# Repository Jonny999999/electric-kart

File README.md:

Firmware for Atmega-8 Microcontroller and kicad PCB-Files for a custom built electric kart.  
**Note:** The firmware and PCB files Version V1 were originally created in 2015, those have been added to this repository for archival purposes.

<br>

# Hardware Overview (vehicle)
- 2.9 kW Series wound motor (forklift)
- Custom pcb with Atmega-8 creating 124 Hz PWM
- Custom pcb with mosfet driver
- Custom pcb with relay on IGBT for emergency stop
- Audi gas pedal used as voltage divider 
- 600A IGBT (FUJI 1MBI600PX-140-01)
- Schottky diode

## Wiring plan
[doc/wiring-plan.drawio.pdf](doc/wiring-plan.drawio.pdf)
  
## Photos

<br>

# Firmware
## Requirements
- avr-gcc
- avrdude
- make

## Compile
```bash
cd firmware/V1_fw-control-board
make
```

## Flash
Connect laptop to the board using an USB ISB-Programmer and run the commands:
```bash
make &&
sudo make upload
```
Note: `make upload` flashes the last compiled .elf file only  
-> also run `make` first for compiling and flashing the latest version.

## Current version
The current actually used project is located in [firmware/V2.1/](firmware/V2.1/).  
All other folders in [firmware/](firmware/) are for old board versions thus no longer used and archive only.

<br>

# Hardware (PCB Versions)
## V2.1
Rework of version V2.0 with more effort put into EMC to fix controller resets:
- 2 layer board
- 5V/GND for controller completely isolated from main batteries
  - isolated 5V DC-DC converter IC
  - more optocouplers: for driver, mosfet, relay and batt-voltage-threshold
- Strictly separate 5V and 24V components (separate GND planes, isolation gap)
- Front side is GND layer, Back side also has GND zones

Date: 2024.08.20  
Folder: [hardware/V2.1_board-ecar_isolated](hardware/V2.1_board-ecar_isolated/)  
Schematic: [hardware/V2.1_board-ecar_isolated/export/schematic.pdf](hardware/V2.1_board-ecar_isolated/export/schematic.pdf)
<br>
<br>

## V2.0
V1.1 worked well for almost 9 years, the idea was to replace the corroded pcb and get rid of the separate supply batteries for the control board.  
Single board with controller, driver and newly added:
- supply filter
- buck converter
- relay  
  
Date: 2024.08.06  
Folder: [hardware/V2.0_board-ecar](hardware/V2.0_board-ecar)  
Schematic: [hardware/V2.0_board-ecar/export/schematic.pdf](hardware/V2.0_board-ecar/export/schematic.pdf)
<br>
<br>

**Fail:**  
Same problems as previous versions: When main batteries are used as supply for control pcb, the controller crashes at certain duty cycle.  
When Using an isolated supply (separate battery or lab supply) there is no issue. => peaks in supply voltage were not the issue and the filter did not really help, except preventing the voltage-regulators from burning out.  
<br>
**Issues:**  
- bad GND track (driver current shifts GND level for controller)
- bad routing overall (EMC)
- UART connector missing
- GND testpin missing

## V1.1
**separate driver board**  
Same control board from V1.0 but additional separate pcb with mosfet driver.  
Date: 2015.05.24  
Folder: [hardware/V1.1_driver-board-separate](hardware/V1.1_driver-board-separate)  
Schematic: [hardware/V1.1_driver-board-separate/export/schematic.pdf](hardware/V1.1_driver-board-separate/export/schematic.pdf)
<br>
<br>

## V1.0
**control board**   
Date: 2015.05.14  
Folder: [hardware/V1.x_control-board](hardware/V1.x_control-board)  
Schematic: [hardware/V1.x_control-board/export/schematic.pdf](hardware/V1.x_control-board/export/schematic.pdf)
<br>
<br>

**Issues:**
- separate battery for control supply is necessary, when using main battery controller crashes when motor starts

**driver board on IGBT**  
pcb on IGBT with mosfet driver and relay (only the relay on this board is still used in V2.1)    
Folder: [hardware/V1.0_driver-board-on-igbt](hardware/V1.0_driver-board-on-igbt)  
Schematic: [hardware/V1.0_driver-board-on-igbt/export/schematic.pdf](hardware/V1.0_driver-board-on-igbt/export/schematic.pdf)
<br>
<br>

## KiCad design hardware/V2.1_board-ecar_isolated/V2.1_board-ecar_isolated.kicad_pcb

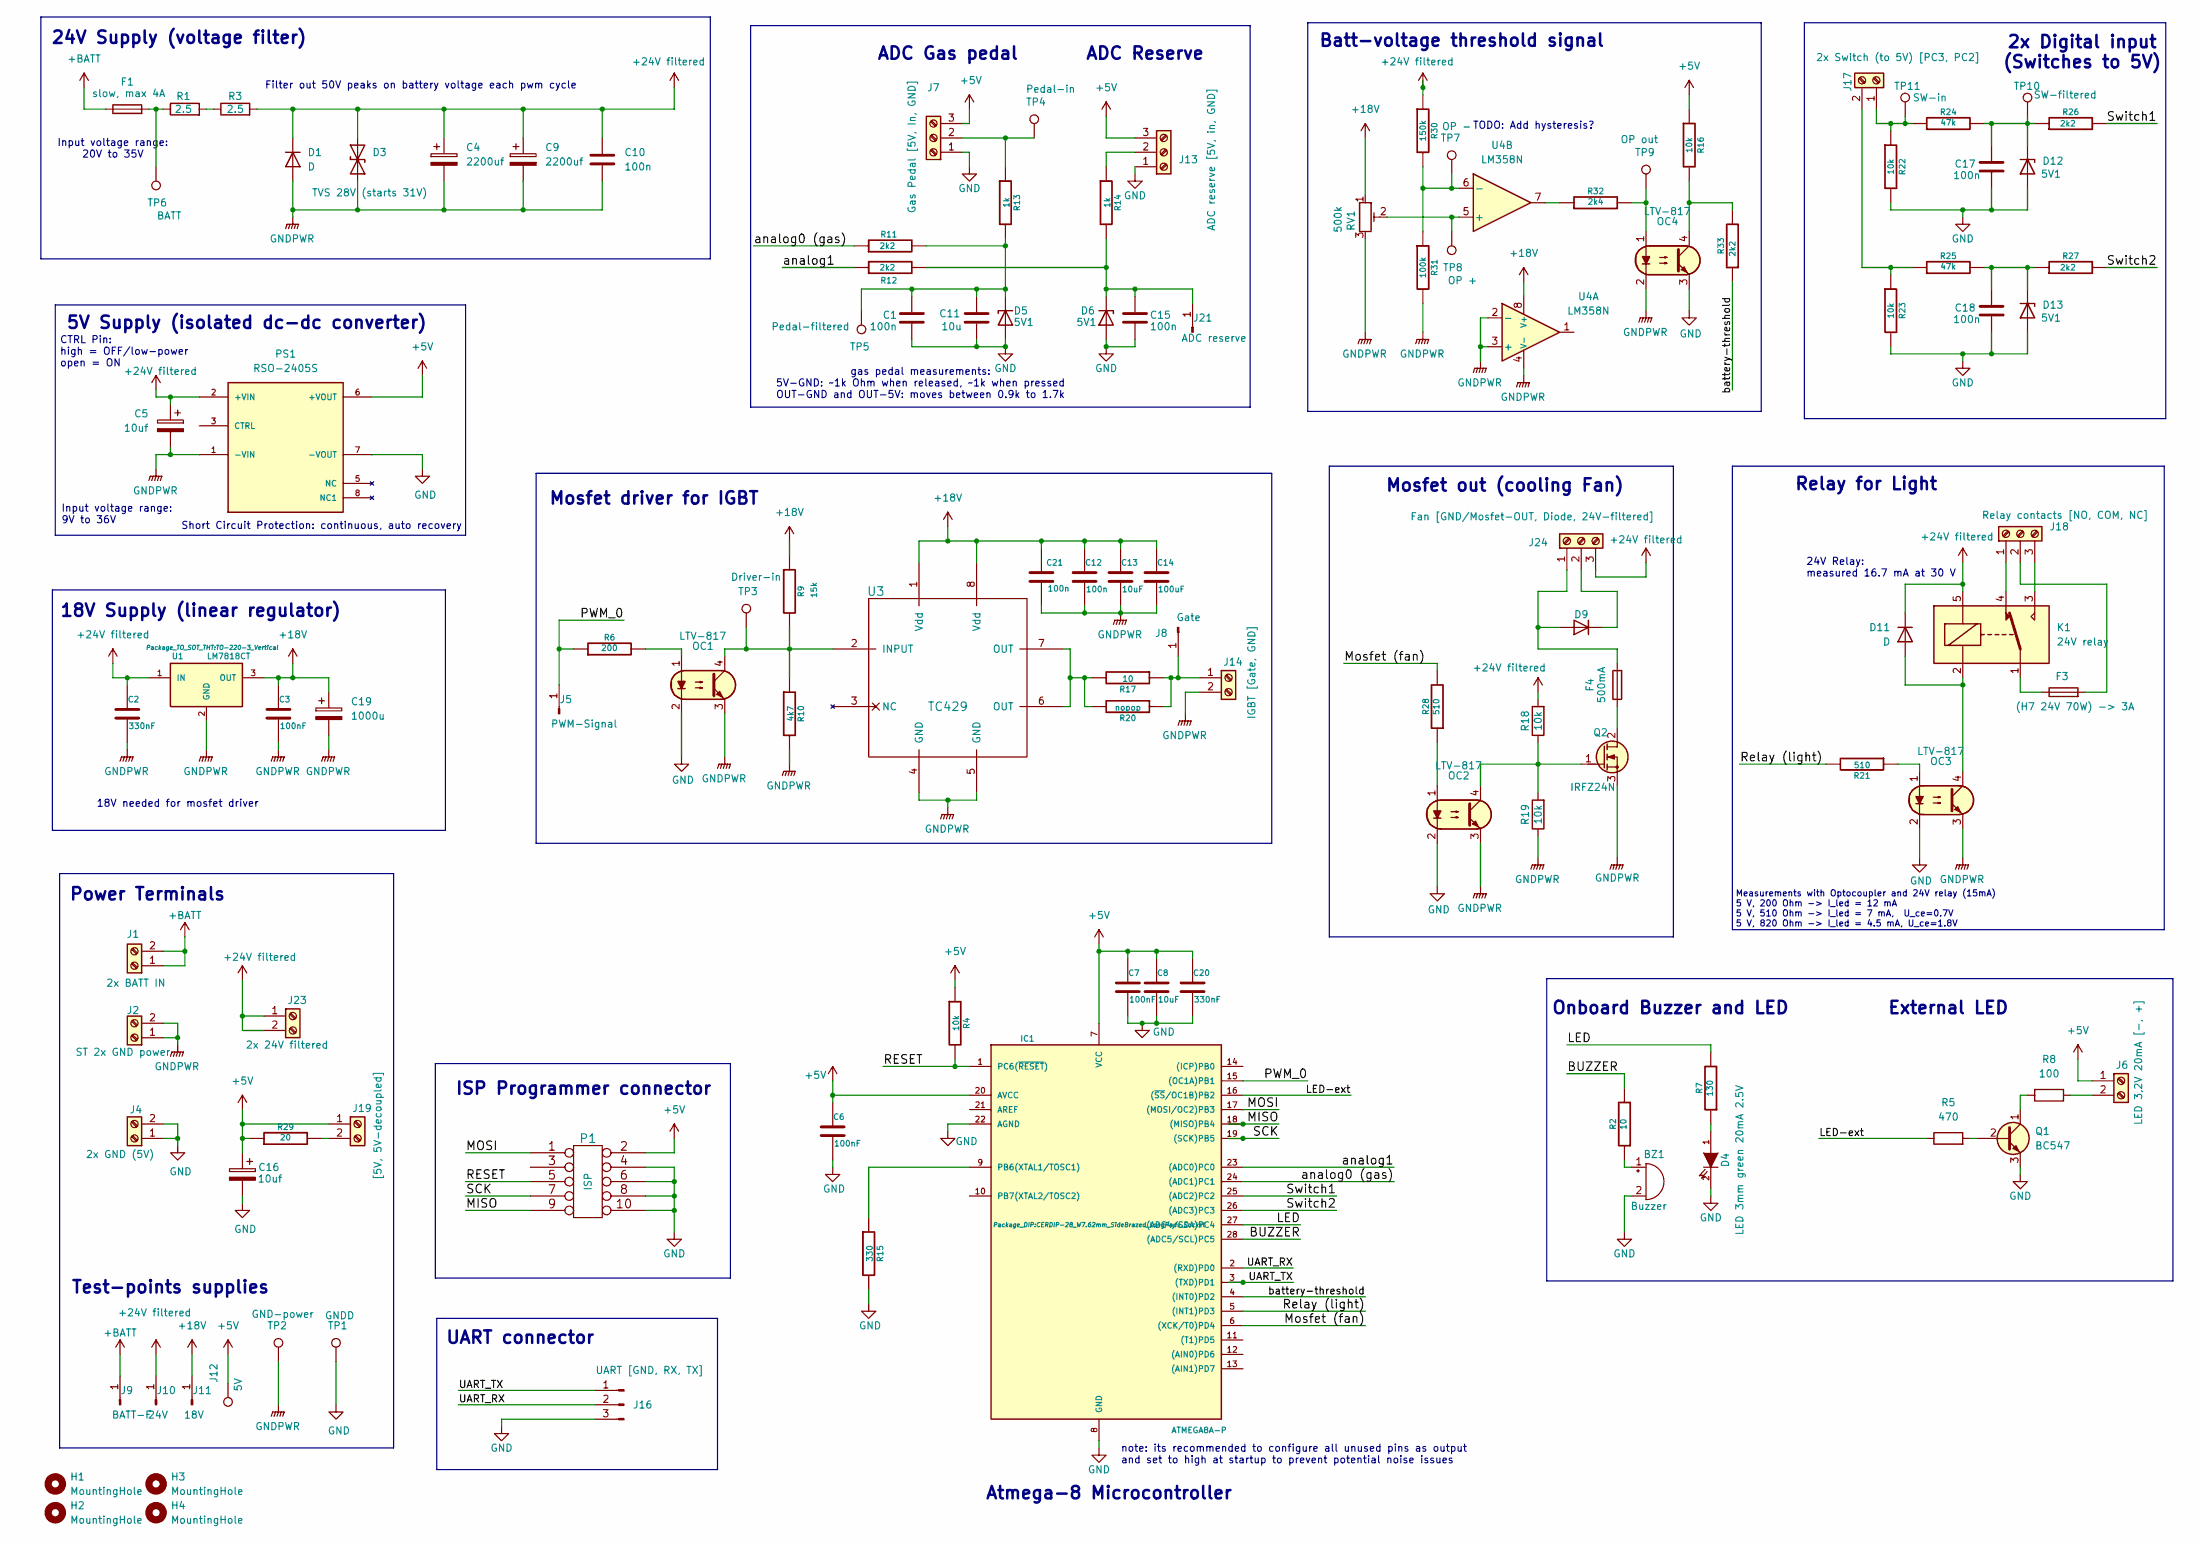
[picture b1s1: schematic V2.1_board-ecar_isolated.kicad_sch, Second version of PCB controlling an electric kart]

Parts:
BZ1: Buzzer; Buzzer_TDK_PS1240P02BT_D12.2mm_H6.5mm
C1, C10, C12, C15, C17, C18, C21: 100n; C_Disc_D7.0mm_W2.5mm_P5.00mm
C2, C20: 330nF; C_Disc_D8.0mm_W5.0mm_P5.00mm
C3, C6, C7: 100nF; C_Disc_D7.0mm_W2.5mm_P5.00mm
C4, C9: 2200uf; CP_Radial_D18.0mm_P7.50mm
C5, C16: 10uf; CP_Radial_D5.0mm_P2.50mm
C8, C13: 10uF; CP_Radial_D5.0mm_P2.50mm
C11: 10u; CP_Radial_D5.0mm_P2.50mm
C14: 100uF; CP_Radial_D8.0mm_P5.00mm
C19: 1000u; CP_Radial_D10.0mm_P5.00mm
D1, D9, D11: D; D_T-1_P12.70mm_Horizontal
D3: TVS 28V (starts 31V); D_DO-201AE_P15.24mm_Horizontal
D4: LED 3mm green 20mA 2.5V; LED_D3.0mm_Clear
D5, D6, D12, D13: 5V1; D_A-405_P10.16mm_Horizontal
F1: slow, max 4A; Fuseholder_Cylinder-5x20mm_Stelvio-Kontek_PTF78_Horizontal_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
F3: (H7 24V 70W) -> 3A; Fuseholder_Cylinder-5x20mm_Stelvio-Kontek_PTF78_Horizontal_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
F4: 500mA; Fuseholder_Cylinder-5x20mm_Stelvio-Kontek_PTF78_Horizontal_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
H1, H2, H3, H4: MountingHole; MountingHole_5.3mm_M5
IC1: ATMEGA8A-P; CERDIP-28_W7.62mm_SideBrazed_LongPads_Socket
J1: 2x BATT IN; TerminalBlock_bornier-2_P5.08mm
J2: ST 2x GND power; TerminalBlock_bornier-2_P5.08mm
J4: 2x GND (5V); TerminalBlock_bornier-2_P5.08mm
J5: PWM-Signal; PinHeader_1x01_P1.00mm_Vertical
J6: LED 3,2V 20mA [-, +]; TerminalBlock_bornier-2_P5.08mm
J7: Gas Pedal [5V, In, GND]; TerminalBlock_bornier-3_P5.08mm
J8: Gate; PinHeader_1x01_P1.00mm_Vertical
J9: BATT-F; PinHeader_1x01_P1.00mm_Vertical
J10: 24V; PinHeader_1x01_P1.00mm_Vertical
J11: 18V; PinHeader_1x01_P1.00mm_Vertical
J12: 5V; PinHeader_1x01_P1.00mm_Vertical
J13: ADC reserve [5V, in, GND]; TerminalBlock_bornier-3_P5.08mm
J14: IGBT [Gate, GND]; TerminalBlock_bornier-2_P5.08mm
J16: UART [GND, RX, TX]; PinHeader_1x03_P2.54mm_Vertical
J17: 2x Switch (to 5V) [PC3, PC2]; TerminalBlock_bornier-2_P5.08mm
J18: Relay contacts [NO, COM, NC]; TerminalBlock_bornier-3_P5.08mm
J19: [5V, 5V-decoupled]; TerminalBlock_bornier-2_P5.08mm
J21: ADC reserve; PinHeader_1x01_P1.00mm_Vertical
J23: 2x 24V filtered; TerminalBlock_bornier-2_P5.08mm
J24: Fan [GND/Mosfet-OUT, Diode, 24V-filtered]; TerminalBlock_bornier-3_P5.08mm
K1: 24V relay; Relay_SPDT_SANYOU_SRD_Series_Form_C
OC1, OC2, OC3, OC4: LTV-817; DIP-4_W10.16mm_LongPads
P1: ISP; IDC-Header_2x05_P2.54mm_Vertical
PS1: RSO-2405S; CONV_RSO-2405S; PARTREV 3
Q1: BC547; TO-92L
Q2: IRFZ24N; TO-220-3_Vertical
R1, R3: 2.5; R_Axial_DIN0922_L20.0mm_D9.0mm_P25.40mm_Horizontal
R2, R17: 10; R_Axial_DIN0207_L6.3mm_D2.5mm_P10.16mm_Horizontal
R4, R16, R18, R19, R22, R23: 10k; R_Axial_DIN0207_L6.3mm_D2.5mm_P10.16mm_Horizontal
R5: 470; R_Axial_DIN0207_L6.3mm_D2.5mm_P10.16mm_Horizontal
R6: 200; R_Axial_DIN0207_L6.3mm_D2.5mm_P10.16mm_Horizontal
R7: 130; R_Axial_DIN0207_L6.3mm_D2.5mm_P10.16mm_Horizontal
R8: 100; R_Axial_DIN0207_L6.3mm_D2.5mm_P10.16mm_Horizontal
R9: 15k; R_Axial_DIN0207_L6.3mm_D2.5mm_P10.16mm_Horizontal
R10: 4k7; R_Axial_DIN0207_L6.3mm_D2.5mm_P10.16mm_Horizontal
R11, R12, R26, R27, R33: 2k2; R_Axial_DIN0207_L6.3mm_D2.5mm_P10.16mm_Horizontal
R13, R14: 1k; R_Axial_DIN0207_L6.3mm_D2.5mm_P10.16mm_Horizontal
R15: 330; R_Axial_DIN0207_L6.3mm_D2.5mm_P10.16mm_Horizontal
R20: nopop; R_Axial_DIN0207_L6.3mm_D2.5mm_P10.16mm_Horizontal
R21, R28: 510; R_Axial_DIN0207_L6.3mm_D2.5mm_P10.16mm_Horizontal
R24, R25: 47k; R_Axial_DIN0207_L6.3mm_D2.5mm_P10.16mm_Horizontal
R29: 20; R_Axial_DIN0207_L6.3mm_D2.5mm_P10.16mm_Horizontal
R30: 150k; R_Axial_DIN0207_L6.3mm_D2.5mm_P10.16mm_Horizontal
R31: 100k; R_Axial_DIN0207_L6.3mm_D2.5mm_P10.16mm_Horizontal
R32: 2k4; R_Axial_DIN0207_L6.3mm_D2.5mm_P10.16mm_Horizontal
RV1: 500k; Potentiometer_Piher_PT-10-V10_Vertical
TP1: GNDD; PinHeader_1x01_P1.00mm_Vertical
TP2: GND-power; PinHeader_1x01_P1.00mm_Vertical
TP3: Driver-in; PinHeader_1x01_P1.00mm_Vertical
TP4: Pedal-in; PinHeader_1x01_P1.00mm_Vertical
TP5: Pedal-filtered; PinHeader_1x01_P1.00mm_Vertical
TP6: BATT; PinHeader_1x01_P1.00mm_Vertical
TP7: OP -; PinHeader_1x01_P1.00mm_Vertical
TP8: OP +; PinHeader_1x01_P1.00mm_Vertical
TP9: OP out; PinHeader_1x01_P1.00mm_Vertical
TP10: SW-filtered; PinHeader_1x01_P1.00mm_Vertical
TP11: SW-in; PinHeader_1x01_P1.00mm_Vertical
U1: LM7818CT; TO-220-3_Vertical
U3: TC429; DIP-8_W7.62mm_Socket_LongPads
U4: LM358N; DIP-8_W7.62mm_LongPads

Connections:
+5V: C6.1, C7.1, C8.1, C16.1, C20.1, IC1.7 (VCC), IC1.20 (AVCC), J6.1, J7.3, J12.1, J13.3, J19.1, P1.2, PS1.6 (+VOUT), R4.1, R16.1, R29.1
+18V: C3.1, C12.1, C13.1, C14.1, C19.1, C21.1, J11.1, R9.1, RV1.1, U1.3 (OUT), U3.1 (Vdd), U3.8 (Vdd), U4.8 (V+)
+24V filtered: C2.1, C4.1, C5.1, C9.1, C10.1, D1.1 (K), D3.2 (A2), D11.1 (K), J10.1, J23.1, J23.2, J24.3, K1.5, PS1.2 (+VIN), R3.2, R18.2, R30.1, U1.1 (IN)
+BATT: F1.1, J1.1, J1.2, J9.1
/BUZZER: IC1.28 ((ADC5/SCL)PC5), R2.2
/LED: IC1.27 ((ADC4/SDA)PC4), R7.2
/LED-ext: IC1.16 ((~SS/OC1B)PB2), R5.1
/MISO: IC1.18 ((MISO)PB4), P1.9
/MOSI: IC1.17 ((MOSI/OC2)PB3), P1.1
/Mosfet (fan): IC1.6 ((XCK/T0)PD4), R28.2
/PWM_0: IC1.15 ((OC1A)PB1), J5.1, R6.1
/RESET: IC1.1 (PC6(~RESET)), P1.5, R4.2
/Relay (light): IC1.5 ((INT1)PD3), R21.2
/SCK: IC1.19 ((SCK)PB5), P1.7
/Switch1: IC1.25 ((ADC2)PC2), R26.2
/Switch2: IC1.26 ((ADC3)PC3), R27.2
/UART_RX: IC1.2 ((RXD)PD0), J16.2
/UART_TX: IC1.3 ((TXD)PD1), J16.1
/analog0 (gas): IC1.24 ((ADC1)PC1), R11.1
/analog1: IC1.23 ((ADC0)PC0), R12.1
/battery-threshold: IC1.4 ((INT0)PD2), R33.1
GND: BZ1.2 (-), C1.2, C6.2, C7.2, C8.2, C11.2, C15.2, C16.2, C17.2, C18.2, C20.2, D4.2 (K), D5.2 (A), D6.2 (A), D12.2 (A), D13.2 (A), IC1.8 (GND), IC1.22 (AGND), J4.1, J4.2, J7.1, J13.1, J16.3, OC1.2, OC2.2, OC3.2, OC4.3, P1.4, P1.6, P1.8, P1.10, PS1.7 (-VOUT), Q1.3 (E), R15.2, R22.2, R23.2, TP1.1
GNDPWR: C2.2, C3.2, C4.2, C5.2, C9.2, C10.2, C12.2, C13.2, C14.2, C19.2, C21.2, D1.2 (A), D3.1 (A1), J2.1, J2.2, J14.2, OC1.3, OC2.3, OC3.3, OC4.2, PS1.1 (-VIN), Q2.3 (S), R10.2, R19.1, R31.2, RV1.3, TP2.1, U1.2 (GND), U3.4 (GND), U3.5 (GND), U4.2 (-), U4.3 (+), U4.4 (V-)
unnamed: BZ1.1 (+), R2.1
unnamed: D4.1 (A), R7.1
unnamed: C1.1, C11.1, D5.1 (K), R11.2, R13.2, TP5.1
unnamed: C15.1, D6.1 (K), J21.1, R12.2, R14.2
unnamed: D9.2 (A), F4.2, J24.1
unnamed: D9.1 (K), J24.2
unnamed: D11.2 (A), K1.2, OC3.4
unnamed: C17.1, D12.1 (K), R24.2, R26.1, TP10.1
unnamed: C18.1, D13.1 (K), R25.2, R27.1
unnamed: F1.2, R1.1, TP6.1
unnamed: F3.1, K1.1
unnamed: IC1.9 (PB6(XTAL1/TOSC1)), R15.1
unnamed: J6.2, R8.1
unnamed: J7.2, R13.1, TP4.1
unnamed: J13.2, R14.1
unnamed: J8.1, J14.1, R17.1, R20.1
unnamed: J17.1, R22.1, R24.1, TP11.1
unnamed: J17.2, R23.1, R25.1
unnamed: J18.1, K1.4
unnamed: F3.2, J18.2
unnamed: J18.3, K1.3
unnamed: J19.2, R29.2
unnamed: OC1.1, R6.2
unnamed: OC2.1, R28.1
unnamed: OC3.1, R21.1
unnamed: OC4.1, R32.2, TP9.1
unnamed: OC4.4, R16.2, R33.2
unnamed: Q1.2 (B), R5.2
unnamed: Q1.1 (C), R8.2
unnamed: F4.1, Q2.2 (D)
unnamed: OC2.4, Q2.1 (G), R18.1, R19.2
unnamed: R1.2, R3.1
unnamed: R17.2, R20.2, U3.6 (OUT), U3.7 (OUT)
unnamed: R32.1, U4.7
unnamed: OC1.4, R9.2, R10.1, TP3.1, U3.2 (INPUT)
unnamed: RV1.2, TP8.1, U4.5 (+)
unnamed: R30.2, R31.1, TP7.1, U4.6 (-)

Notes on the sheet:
ADC Reserve
Batt-voltage threshold signal
ISP Programmer connector
Atmega-8 Microcontroller
Onboard Buzzer and LED
note: its recommended to configure all unused pins as output and set to high at startup to prevent potential noise issues
ADC Gas pedal
Mosfet driver for IGBT
18V needed for mosfet driver
TODO: Add hysteresis?
Power Terminals
24V Supply (voltage filter)
Input voltage range: 20V to 35V
5V Supply (isolated dc-dc converter)
Test-points supplies
18V Supply (linear regulator)
2x Digital input (Switches to 5V)
24V Relay: measured 16.7 mA at 30 V
Short Circuit Protection: continuous, auto recovery
Filter out 50V peaks on battery voltage each pwm cycle
UART connector
gas pedal measurements: 5V-GND: ~1k Ohm when released, ~1k when pressed OUT-GND and OUT-5V: moves between 0.9k to 1.7k
CTRL Pin: high = OFF/low-power open = ON
Input voltage range: 9V to 36V
External LED
Measurements with Optocoupler and 24V relay (15mA) 5 V, 200 Ohm -> I_led = 12 mA 5 V, 510 Ohm -> I_led = 7 mA, U_ce=0.7V 5 V, 820 Ohm -> I_led = 4.5 mA, U_ce=1.8V
Mosfet out (cooling Fan)
Relay for Light

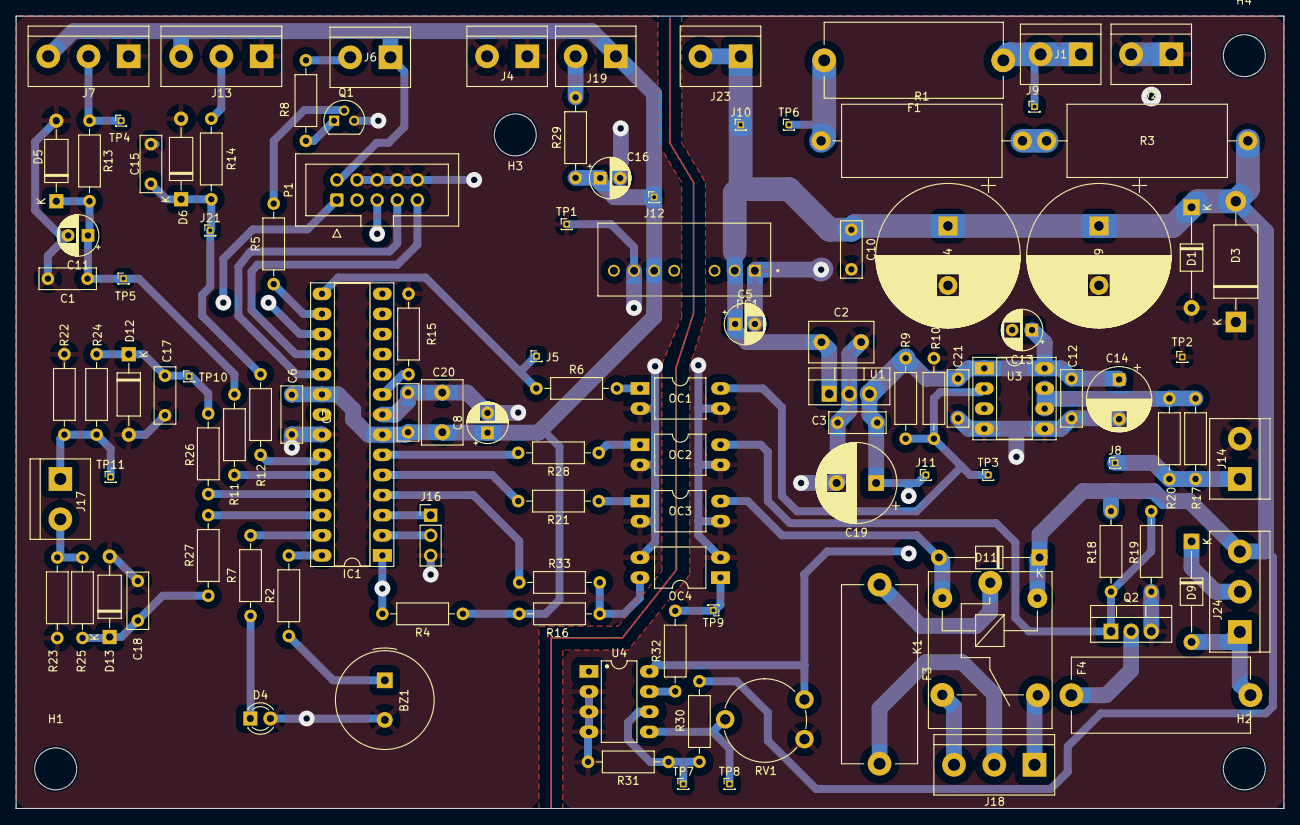
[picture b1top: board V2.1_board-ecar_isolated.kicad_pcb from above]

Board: 4 copper layers, 160.0 x 100.0 mm, 116 parts (0 on the bottom side), 60 nets.

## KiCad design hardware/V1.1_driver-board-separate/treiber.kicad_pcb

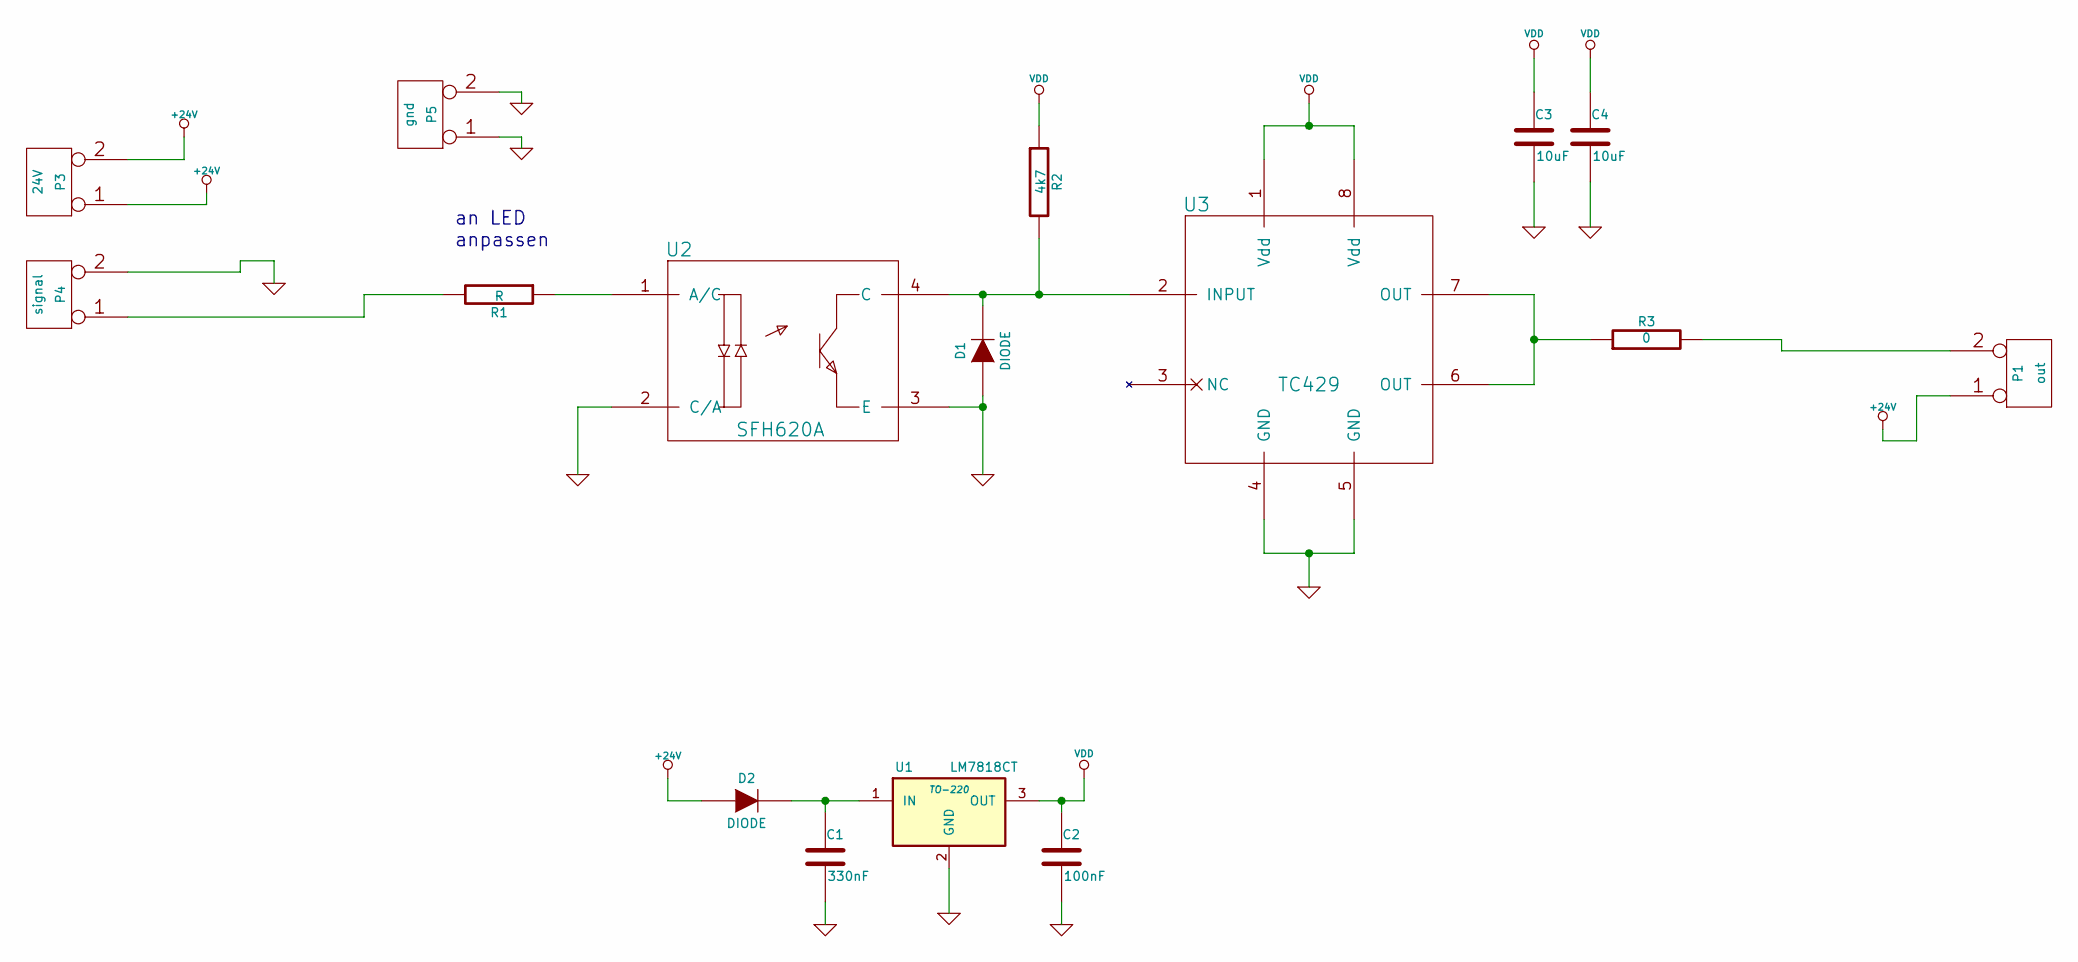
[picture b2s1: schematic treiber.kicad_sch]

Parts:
C1: 330nF
C2: 100nF
C3, C4: 10uF
D1, D2: DIODE
P1: out
P3: 24V
P4: signal
P5: gnd
R1: R
R2: 4k7
R3: 0
U1: LM7818CT; TO-220
U2: SFH620A
U3: TC429

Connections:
+24V: D2.1 (A), P1.1, P3.1, P3.2 (PM)
GND: C1.2, C2.2, C3.2, C4.2, D1.1 (A), P4.2 (PM), P5.1, P5.2 (PM), U1.2 (GND), U2.2 (C/A), U2.3 (E), U3.4 (GND), U3.5 (GND)
unnamed: P4.1, R1.2
unnamed: P1.2 (PM), R3.2
unnamed: R3.1, U3.6 (OUT), U3.7 (OUT)
unnamed: C1.1, D2.2 (K), U1.1 (IN)
unnamed: D1.2 (K), R2.2, U2.4 (C), U3.2 (INPUT)
unnamed: R1.1, U2.1 (A/C)
VDD: C2.1, C3.1, C4.1, R2.1, U1.3 (OUT), U3.1 (Vdd), U3.8 (Vdd)

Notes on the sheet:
an LED anpassen

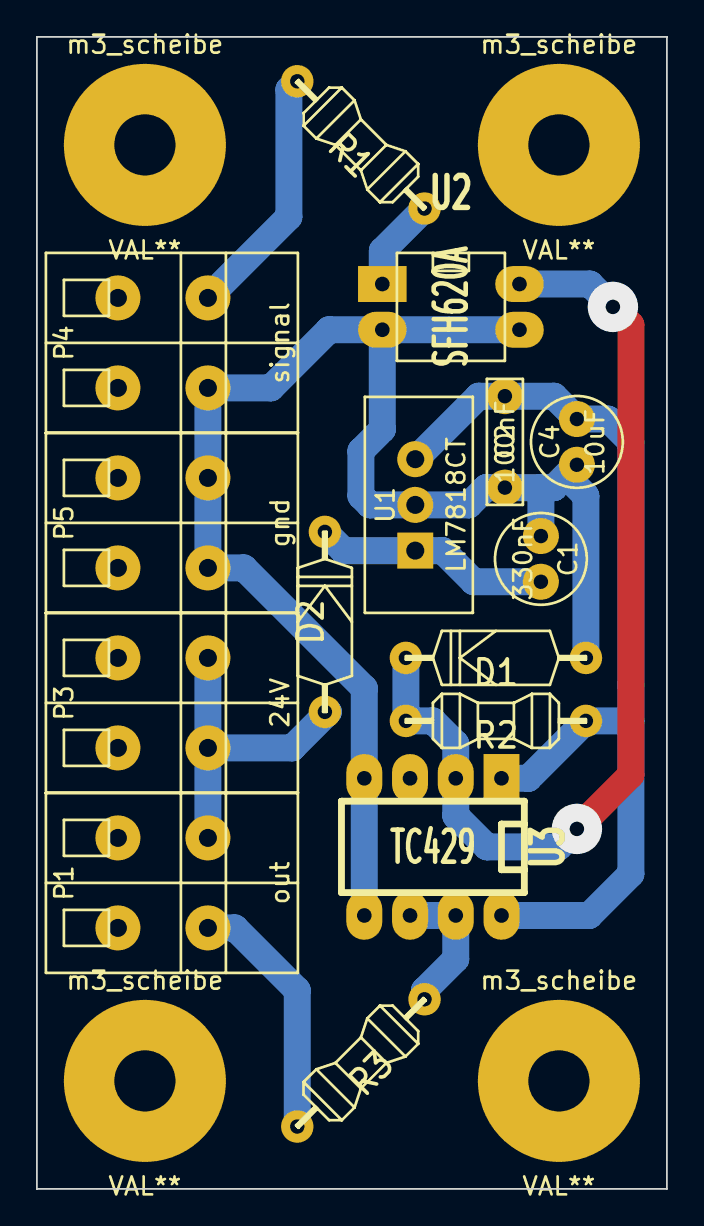
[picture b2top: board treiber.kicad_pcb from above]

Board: 2 copper layers, 35.0 x 64.0 mm, 19 parts (0 on the bottom side), 9 nets.

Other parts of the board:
m3_scheibe, m3_scheibe#2, m3_scheibe#3, m3_scheibe#4: VAL**; m3_scheibe

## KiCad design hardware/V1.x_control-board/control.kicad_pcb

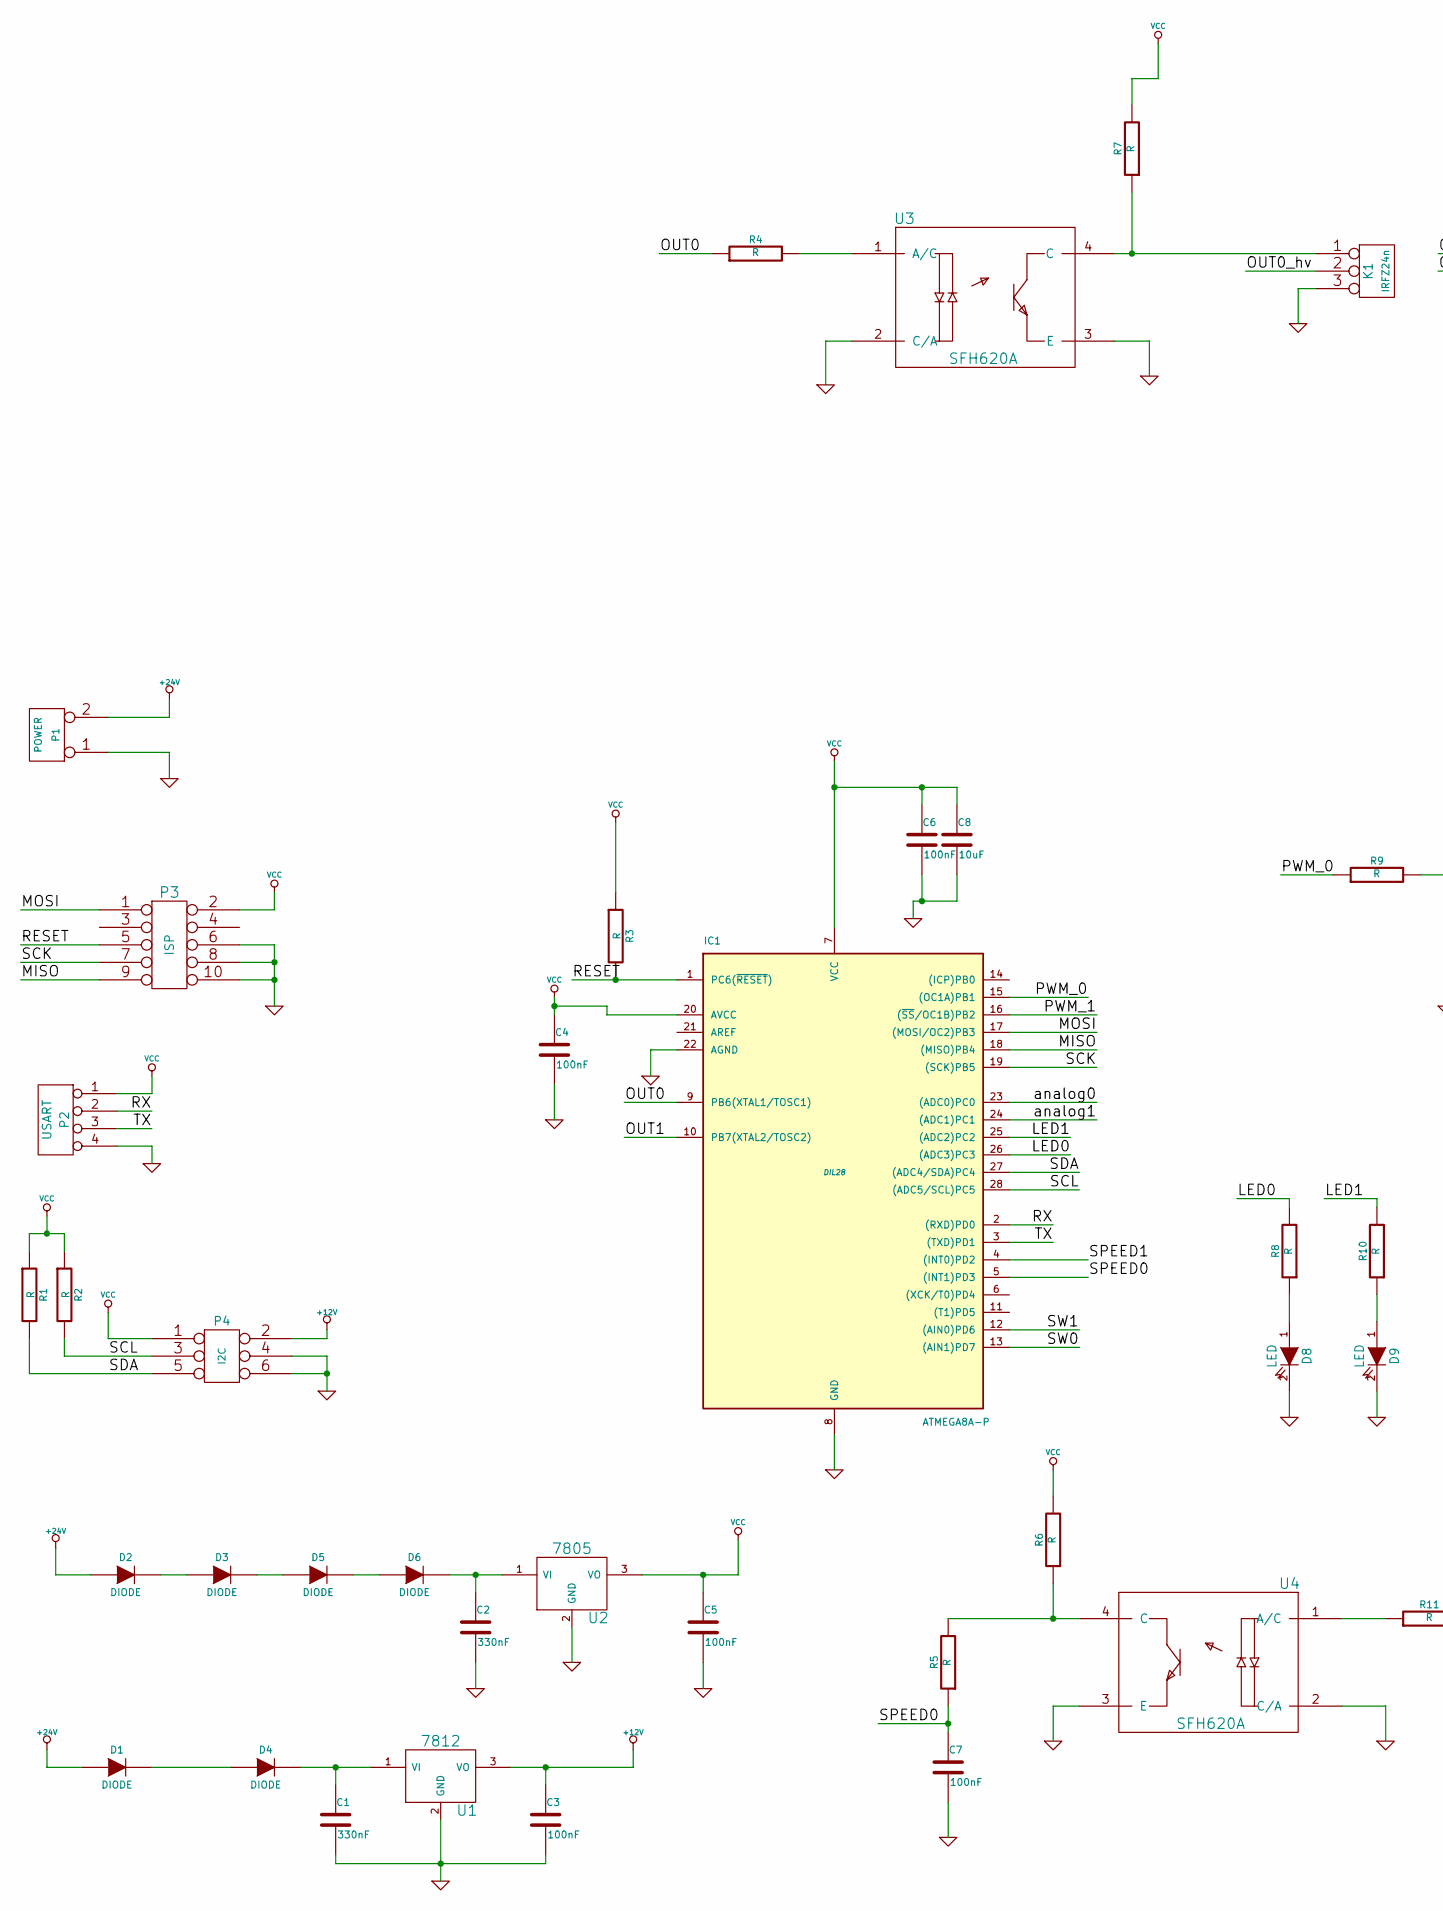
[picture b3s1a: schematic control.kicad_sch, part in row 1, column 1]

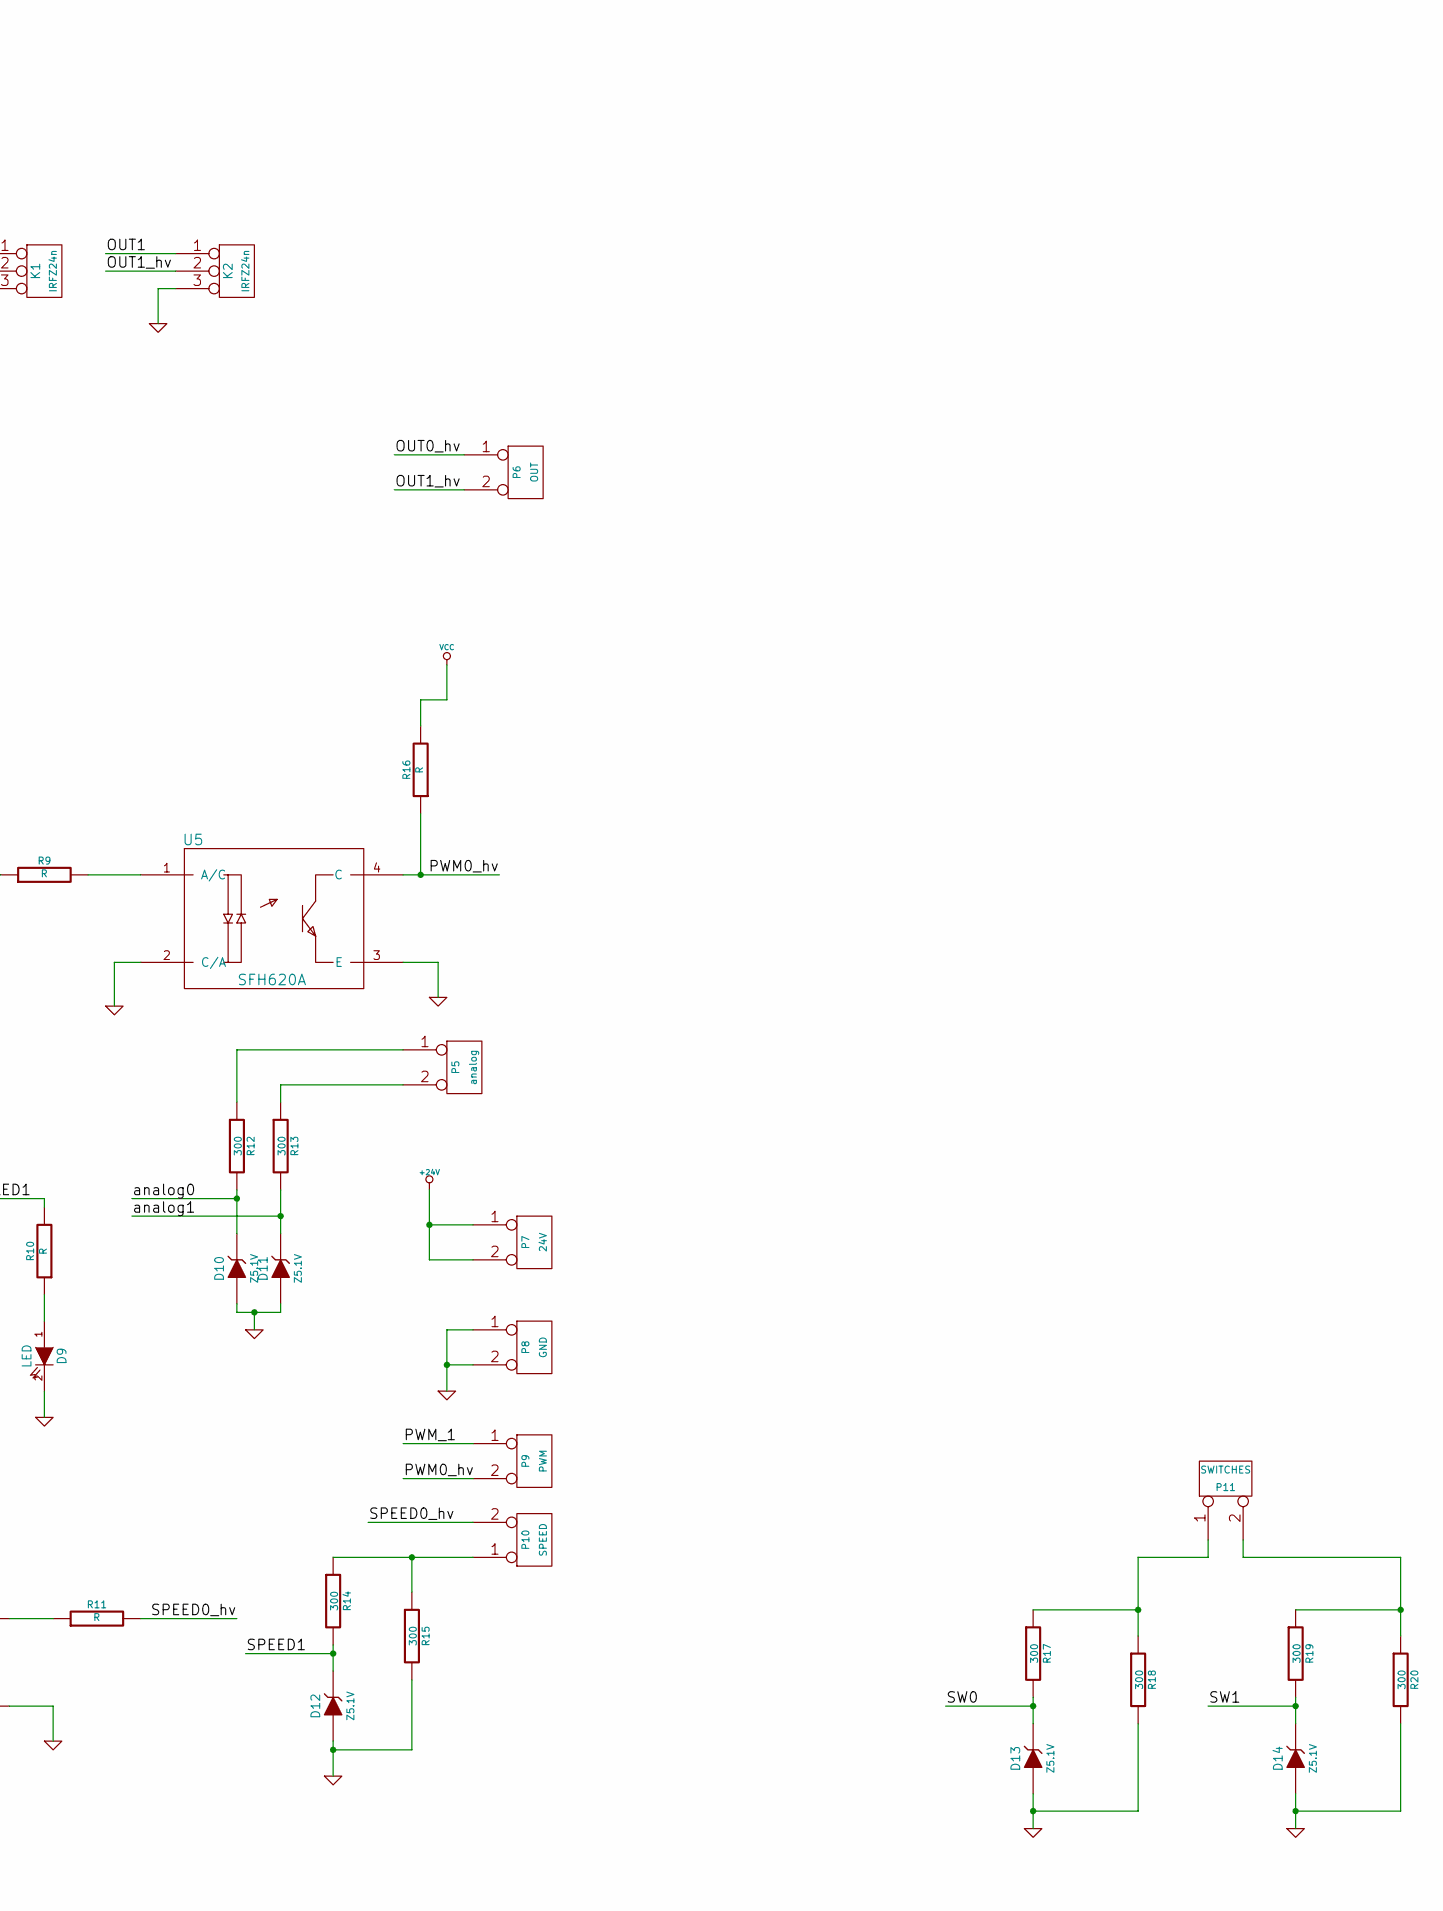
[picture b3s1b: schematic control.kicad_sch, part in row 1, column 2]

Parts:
C1, C2: 330nF
C3, C4, C5, C6, C7: 100nF
C8: 10uF
D1, D2, D3, D4, D5, D6: DIODE
D8, D9: LED
D10, D11, D12, D13, D14: Z5.1V
IC1: ATMEGA8A-P; DIL28
K1, K2: IRFZ24n
P1: POWER
P2: USART
P3: ISP
P4: I2C
P5: analog
P6: OUT
P7: 24V
P8: GND
P9: PWM
P10: SPEED
P11: SWITCHES
R1, R2, R3, R4, R5, R6, R7, R8, R9, R10, R11, R16: R
R12, R13, R14, R15, R17, R18, R19, R20: 300
U1: 7812
U2: 7805
U3, U4, U5: SFH620A

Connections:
+12V: C3.1, P4.2, U1.3 (VO)
+24V: D1.1 (A), D2.1 (A), P1.2 (PM), P7.1, P7.2 (PM)
/LED0: IC1.26 ((ADC3)PC3), R8.2
/LED1: IC1.25 ((ADC2)PC2), R10.2
/MISO: IC1.18 ((MISO)PB4), P3.9
/MOSI: IC1.17 ((MOSI/OC2)PB3), P3.1
/OUT0: IC1.9 (PB6(XTAL1/TOSC1)), R4.1
/OUT0_hv: K1.2 (PM), P6.1
/OUT1: IC1.10 (PB7(XTAL2/TOSC2)), K2.1
/OUT1_hv: K2.2 (PM), P6.2 (PM)
/PWM0_hv: P9.2 (PM), R16.1, U5.4 (C)
/PWM_0: IC1.15 ((OC1A)PB1), R9.1
/PWM_1: IC1.16 ((~SS/OC1B)PB2), P9.1
/RESET: IC1.1 (PC6(~RESET)), P3.5, R3.2
/RX: IC1.2 ((RXD)PD0), P2.2
/SCK: IC1.19 ((SCK)PB5), P3.7
/SCL: IC1.28 ((ADC5/SCL)PC5), P4.3, R2.2
/SDA: IC1.27 ((ADC4/SDA)PC4), P4.5, R1.2
/SPEED0: C7.1, IC1.5 ((INT1)PD3), R5.1
/SPEED0_hv: P10.2 (PM), R11.2
/SPEED1: D12.2 (K), IC1.4 ((INT0)PD2), R14.2
/SW0: D13.2 (K), IC1.13 ((AIN1)PD7), R17.2
/SW1: D14.2 (K), IC1.12 ((AIN0)PD6), R19.2
/TX: IC1.3 ((TXD)PD1), P2.3
/analog0: D10.2 (K), IC1.23 ((ADC0)PC0), R12.2
/analog1: D11.2 (K), IC1.24 ((ADC1)PC1), R13.2
GND: C1.2, C2.2, C3.2, C4.2, C5.2, C6.2, C7.2, C8.2, D8.2 (K), D9.2 (K), D10.1 (A), D11.1 (A), D12.1 (A), D13.1 (A), D14.1 (A), IC1.8 (GND), IC1.22 (AGND), K1.3, K2.3, P1.1, P2.4, P3.6, P3.8, P3.10, P4.4, P4.6, P8.1, P8.2 (PM), R15.2, R18.2, R20.2, U1.2 (GND), U2.2 (GND), U3.2 (C/A), U3.3 (E), U4.2 (C/A), U4.3 (E), U5.2 (C/A), U5.3 (E)
unnamed: P11.2 (PM), R19.1, R20.1
unnamed: P11.1, R17.1, R18.1
unnamed: R5.2, R6.1, U4.4 (C)
unnamed: R11.1, U4.1 (A/C)
unnamed: P5.1, R12.1
unnamed: P5.2 (PM), R13.1
unnamed: K1.1, R7.1, U3.4 (C)
unnamed: R4.2, U3.1 (A/C)
unnamed: D8.1 (A), R8.1
unnamed: D9.1 (A), R10.1
unnamed: P10.1, R14.1, R15.1
unnamed: R9.2, U5.1 (A/C)
unnamed: D1.2 (K), D4.1 (A)
unnamed: C1.1, D4.2 (K), U1.1 (VI)
unnamed: D5.2 (K), D6.1 (A)
unnamed: D2.2 (K), D3.1 (A)
unnamed: D3.2 (K), D5.1 (A)
unnamed: C2.1, D6.2 (K), U2.1 (VI)
VCC: C4.1, C5.1, C6.1, C8.1, IC1.7 (VCC), IC1.20 (AVCC), P2.1, P3.2, P4.1, R1.1, R2.1, R3.1, R6.2, R7.2, R16.2, U2.3 (VO)

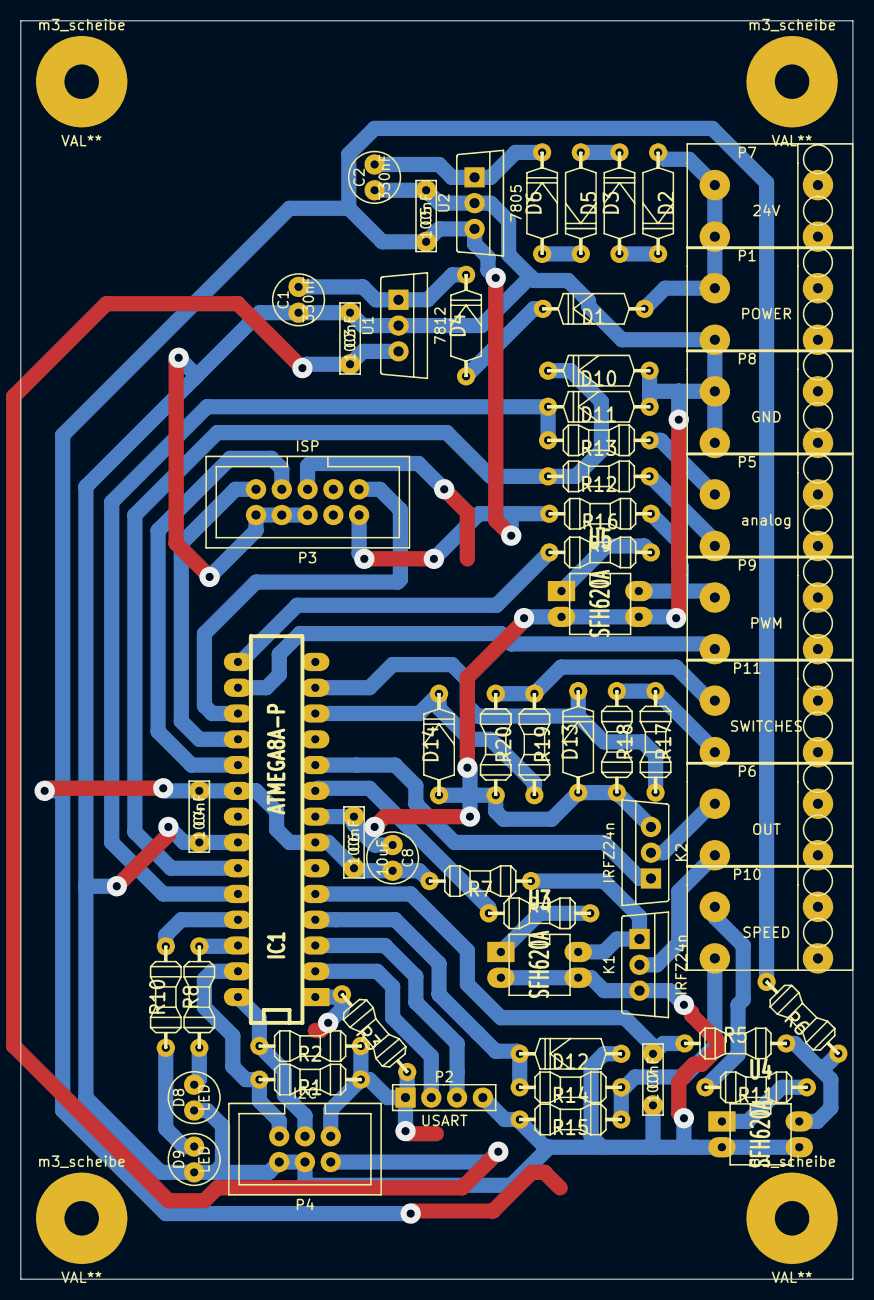
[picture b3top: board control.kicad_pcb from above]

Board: 2 copper layers, 82.0 x 124.0 mm, 64 parts (0 on the bottom side), 46 nets.

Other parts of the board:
m3_scheibe, m3_scheibe#2, m3_scheibe#3, m3_scheibe#4: VAL**; m3_scheibe
